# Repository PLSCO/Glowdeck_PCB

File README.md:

# Glowdeck_PCB
Glowdeck circuit board design and layout

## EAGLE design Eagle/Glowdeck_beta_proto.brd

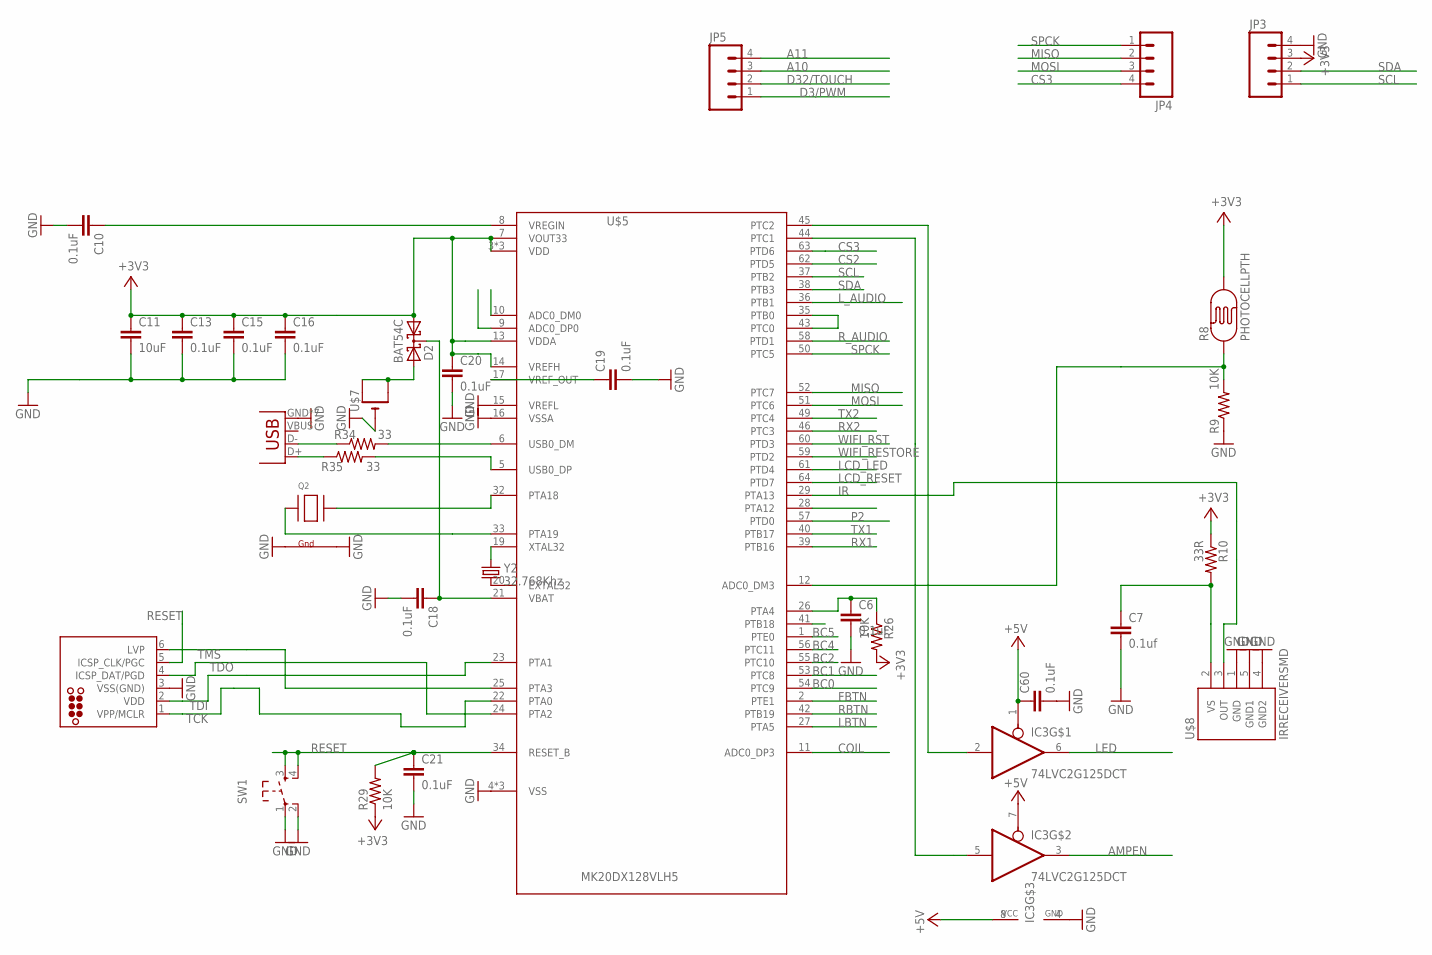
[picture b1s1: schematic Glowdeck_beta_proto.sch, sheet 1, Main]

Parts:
C6, C10, C13, C15, C16, C18, C19, C20, C21, C60: 0.1uF; 0603-CAP
C7: 0.1uf; 0603-CAP
C11: 10uF; 0805
D2: BAT54C; SOT23
IC3: 74LVC2G125DCT; SSOP08
J2: TC2030-MCP-NL
JP3, JP4, JP5: M04LOCK; 1X04_LOCK
Q2: XTAL-4-3225; NX3225
R8: PHOTOCELLPTH; PHOTOCELL
R9, R26, R29: 10K; 0603-RES
R10: 33R; 0603-RES
R34, R35: 33; 0603-RES
SW1: SW_TACT_4P; SW_TACT_SMALL
U$5: MK20DX128VLH5
U$7: CR1220THM; CR1220-THM
U$8: IRRECEIVERSMD; TSOP8523
X3: USB-MICROB
Y2: 32.768Khz; RESONATOR_EPSON_FC_145

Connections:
+3V3: C11.1, C13.1, C15.1, C16.1, C20.1, D2.1 (A1), JP3.3, R8.2, R10.1, R26.2, R29.1, U$5.3 (VDD), U$5.7 (VOUT33), U$5.13 (VDDA), U$5.14 (VREFH), U$5.30 (VDD), U$5.48 (VDD); also elsewhere on the board
+5V: C60.1, IC3.1 (OE), IC3.7 (OE), IC3.8 (VCC); also elsewhere on the board
A10: JP5.3, U$5.9 (ADC0_DP0)
A11: JP5.4, U$5.10 (ADC0_DM0)
AMPEN: IC3.3 (O); also elsewhere on the board
BC0: U$5.54 (PTC9); also elsewhere on the board
BC1: U$5.53 (PTC8); also elsewhere on the board
BC2: U$5.55 (PTC10); also elsewhere on the board
BC4: U$5.56 (PTC11); also elsewhere on the board
BC5: U$5.1 (PTE0); also elsewhere on the board
COIL: U$5.11 (ADC0_DP3); also elsewhere on the board
CS2: U$5.62 (PTD5); also elsewhere on the board
CS3: JP4.4, U$5.63 (PTD6)
D3/PWM: JP5.1, U$5.28 (PTA12)
D32/TOUCH: JP5.2, U$5.41 (PTB18)
FBTN: U$5.2 (PTE1); also elsewhere on the board
GND: C6.2, C7.2, C10.2, C11.2, C13.2, C15.2, C16.2, C18.2, C19.2, C20.2, C21.2, C60.2, IC3.4 (GND), J2.3 (VSS(GND)), JP3.4, Q2.2 (G2), Q2.4 (G1), R9.1, SW1.1, SW1.2, U$5.4 (VSS), U$5.15 (VREFL), U$5.16 (VSSA), U$5.31 (VSS), U$5.47 (VSS), U$7.-, U$8.1 (GND), U$8.4 (GND2), U$8.5 (GND1), X3.GND, X3.P1 (GND), X3.P2 (GND), X3.P3 (GND), X3.P4 (GND), X3.P5 (GND), X3.P6 (GND); also elsewhere on the board
IR: U$5.29 (PTA13), U$8.3 (OUT)
LBTN: U$5.27 (PTA5); also elsewhere on the board
LCD_LED: U$5.61 (PTD4); also elsewhere on the board
LCD_RESET: U$5.64 (PTD7); also elsewhere on the board
LED: IC3.6 (O); also elsewhere on the board
L_AUDIO: U$5.36 (PTB1); also elsewhere on the board
MISO: JP4.2, U$5.52 (PTC7); also elsewhere on the board
MOSI: JP4.3, U$5.51 (PTC6); also elsewhere on the board
unnamed: U$5.35 (PTB0), U$5.43 (PTC0)
unnamed: C7.1, R10.2, U$8.2 (VS)
unnamed: Q2.3 (X2), U$5.32 (PTA18)
unnamed: D2.2 (A2), U$7.+1 (+), U$7.+2 (+1)
unnamed: C6.1, R26.1, U$5.26 (PTA4)
unnamed: U$5.20 (EXTAL32), Y2.P$2 (2)
unnamed: C19.1, U$5.17 (VREF_OUT)
unnamed: C10.1, U$5.8 (VREGIN)
unnamed: C18.1, D2.3 (CC), U$5.21 (VBAT)
unnamed: R34.2, U$5.6 (USB0_DM)
unnamed: R35.2, U$5.5 (USB0_DP)
unnamed: U$5.19 (XTAL32), Y2.P$1 (1)
unnamed: Q2.1 (X1), U$5.33 (PTA19)
unnamed: R8.1, R9.2, U$5.12 (ADC0_DM3)
unnamed: IC3.5 (I), U$5.44 (PTC1)
unnamed: IC3.2 (I), U$5.45 (PTC2)
unnamed: R34.1, X3.D-
unnamed: R35.1, X3.D+
P2: U$5.57 (PTD0); also elsewhere on the board
RBTN: U$5.42 (PTB19); also elsewhere on the board
RESET: C21.1, J2.5 (ICSP_CLK/PGC), R29.2, SW1.3, SW1.4, U$5.34 (RESET_B)
RX1: U$5.39 (PTB16); also elsewhere on the board
RX2: U$5.46 (PTC3); also elsewhere on the board
R_AUDIO: U$5.58 (PTD1); also elsewhere on the board
SCL: JP3.1, U$5.37 (PTB2)
SDA: JP3.2, U$5.38 (PTB3)
SPCK: JP4.1, U$5.50 (PTC5); also elsewhere on the board
TCK: J2.1 (VPP/MCLR), U$5.22 (PTA0)
TDI: J2.2 (VDD), U$5.23 (PTA1)
TDO: J2.4 (ICSP_DAT/PGD), U$5.24 (PTA2)
TMS: J2.6 (LVP), U$5.25 (PTA3)
TX1: U$5.40 (PTB17); also elsewhere on the board
TX2: U$5.49 (PTC4); also elsewhere on the board
WIFI_RESTORE: U$5.59 (PTD2); also elsewhere on the board
WIFI_RST: U$5.60 (PTD3); also elsewhere on the board

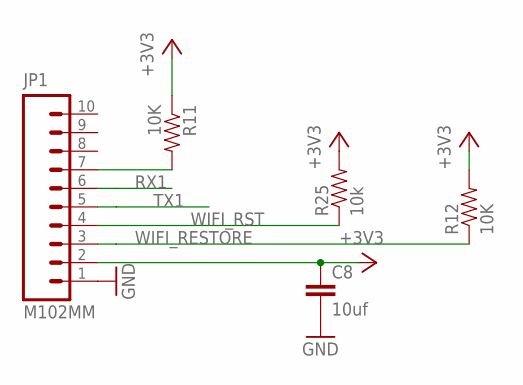
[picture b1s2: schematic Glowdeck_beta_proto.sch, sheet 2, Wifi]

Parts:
C8: 10uf; 0805
JP1: M102MM; 1X10-2MM
R11, R12: 10K; 0603-RES
R25: 10k; 0603-RES

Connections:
+3V3: C8.1, JP1.2, R11.1, R12.2, R25.2; also elsewhere on the board
GND: C8.2, JP1.1; also elsewhere on the board
unnamed: JP1.7, R11.2
RX1: JP1.6; also elsewhere on the board
TX1: JP1.5; also elsewhere on the board
WIFI_RESTORE: JP1.3, R12.1; also elsewhere on the board
WIFI_RST: JP1.4, R25.1; also elsewhere on the board

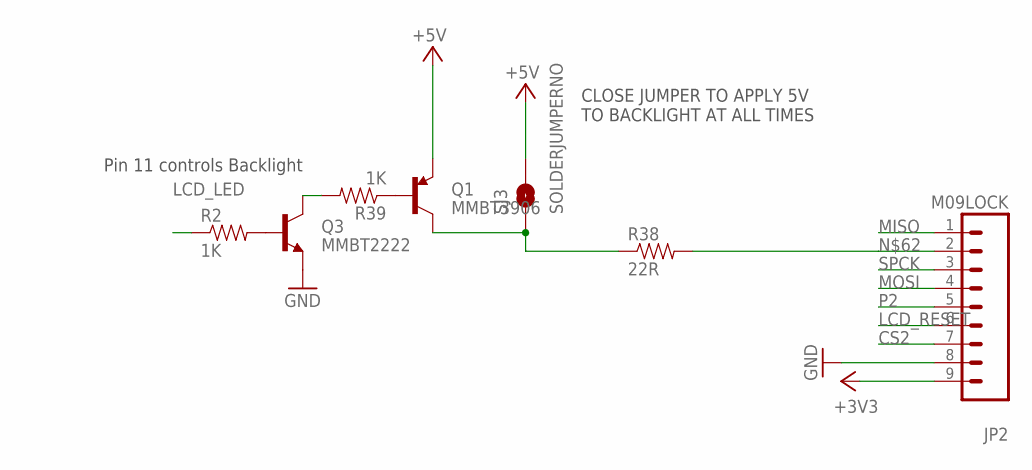
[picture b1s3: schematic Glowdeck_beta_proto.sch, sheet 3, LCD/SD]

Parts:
JP2: M09LOCK; 1X09_LOCK
Q1: MMBT3906; SOT23-3
Q3: MMBT2222; SOT23-3
R2, R39: 1K; 0603-RES
R38: 22R; 1206
SJ3: SOLDERJUMPERNO; SJ_2S-NO

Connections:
+3V3: JP2.9; also elsewhere on the board
+5V: Q1.2 (E), SJ3.2; also elsewhere on the board
BACKLIGHT: Q1.3 (C), R38.1, SJ3.1
CS2: JP2.7; also elsewhere on the board
GND: JP2.8, Q3.2 (E); also elsewhere on the board
LCD_LED: R2.1; also elsewhere on the board
LCD_RESET: JP2.6; also elsewhere on the board
MISO: JP2.1; also elsewhere on the board
MOSI: JP2.4; also elsewhere on the board
unnamed: Q1.1 (B), R39.1
unnamed: JP2.2, R38.2
unnamed: Q3.3 (C), R39.2
unnamed: Q3.1 (B), R2.2
P2: JP2.5; also elsewhere on the board
SPCK: JP2.3; also elsewhere on the board

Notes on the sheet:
CLOSE JUMPER TO APPLY 5V TO BACKLIGHT AT ALL TIMES
Pin 11 controls Backlight

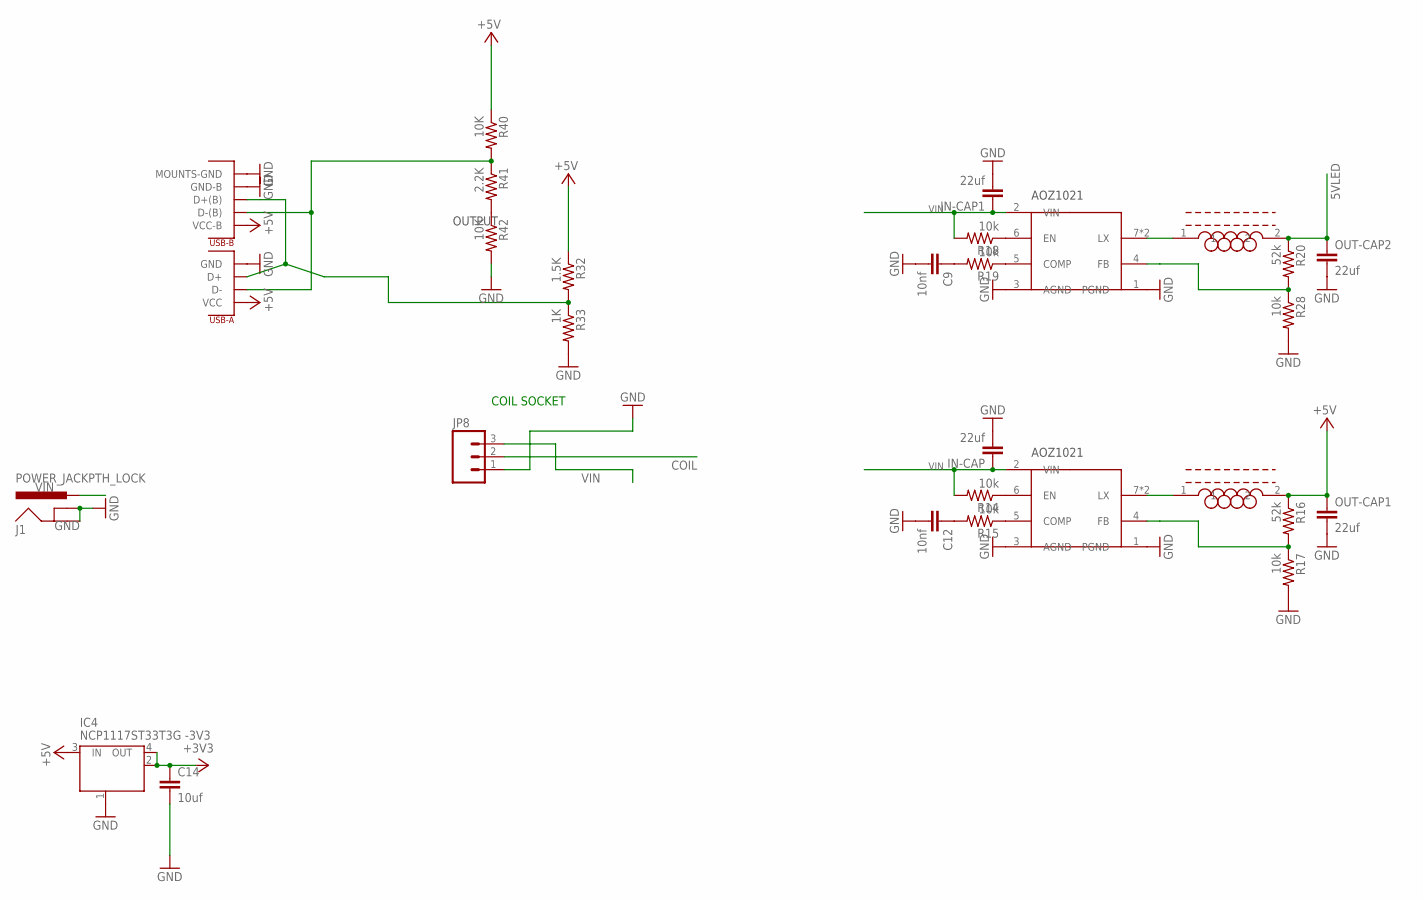
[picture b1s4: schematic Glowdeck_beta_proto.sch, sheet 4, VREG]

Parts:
AOZ1015AI, AOZ1015AI1: AOZ1021; SO-08
C9, C12: 10nf; 0603-CAP
C14: 10uf; 0805
IC4: NCP1117ST33T3G -3V3; SOT223
IN-CAP, IN-CAP1: 22uf; 1210
J1: POWER_JACKPTH_LOCK; POWER_JACK_PTH_LOCK
JP8: M03JST-PTH; JST-3-PTH
OUT-CAP1, OUT-CAP2: 22uf; 1210
R14, R15, R17, R18, R19, R28: 10k; 0603-RES
R16, R20: 52k; 0603-RES
R32: 1.5K; 0603-RES
R33: 1K; 0603-RES
R40, R42: 10K; 0603-RES
R41: 2.2K; 0603-RES
U$1, U$2: SRP7030F; SRP7030
U$6: DUAL-PORT-USB-REC; DUAL-PORT-USB

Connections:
5VLED: OUT-CAP2.1, R20.1, U$2.2; also elsewhere on the board
+3V3: C14.1, IC4.2 (OUT), IC4.4 (OUT); also elsewhere on the board
+5V: IC4.3 (IN), OUT-CAP1.1, R16.1, R32.1, R40.1, U$1.2, U$6.P$10 (VCC-B), U$6.P$12 (VCC); also elsewhere on the board
COIL: JP8.2; also elsewhere on the board
GND: AOZ1015AI.1 (PGND), AOZ1015AI.3 (AGND), AOZ1015AI1.1 (PGND), AOZ1015AI1.3 (AGND), C9.2, C12.2, C14.2, IC4.1 (GND/ADJ), IN-CAP.2, IN-CAP1.2, J1.GND, J1.GNDBREAK, JP8.1, OUT-CAP1.2, OUT-CAP2.2, R17.2, R28.2, R33.2, R42.2, U$6.GND (MOUNTS-GND), U$6.P$2 (MOUNTS-GND), U$6.P$3 (MOUNTS-GND), U$6.P$4 (MOUNTS-GND), U$6.P$9 (GND-B), U$6.P$11 (GND); also elsewhere on the board
LOUT: AOZ1015AI.7 (LX), AOZ1015AI.8 (LX), U$1.1
LOUT1: AOZ1015AI1.7 (LX), AOZ1015AI1.8 (LX), U$2.1
unnamed: AOZ1015AI1.6 (EN), R18.1
unnamed: AOZ1015AI.6 (EN), R14.1
unnamed: AOZ1015AI1.5 (COMP), R19.1
unnamed: C9.1, R19.2
unnamed: AOZ1015AI.5 (COMP), R15.1
unnamed: C12.1, R15.2
unnamed: AOZ1015AI.4 (FB), R16.2, R17.1
unnamed: AOZ1015AI1.4 (FB), R20.2, R28.1
unnamed: R32.2, R33.1, U$6.P$6 (D+(B)), U$6.P$8 (D+)
unnamed: R41.2, R42.1
unnamed: R40.2, R41.1, U$6.P$5 (D-(B)), U$6.P$7 (D-)
VIN: AOZ1015AI.2 (VIN), AOZ1015AI1.2 (VIN), IN-CAP.1, IN-CAP1.1, J1.PWR, JP8.3, R14.2, R18.2; also elsewhere on the board

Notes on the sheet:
OUTPUT
COIL SOCKET

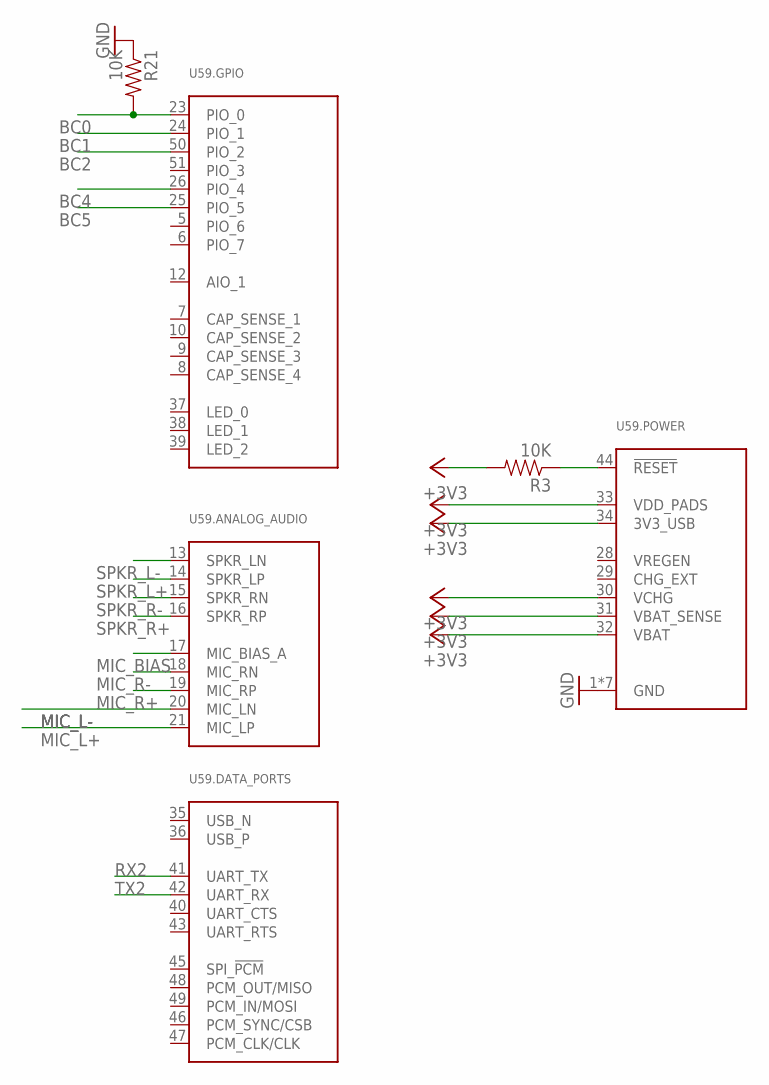
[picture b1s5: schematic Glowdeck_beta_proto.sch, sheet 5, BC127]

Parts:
R3, R21: 10K; 0603-RES
U59: BC127EXTRA_PASTE; BC127_XTRA_PASTE

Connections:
+3V3: R3.2, U59.30 (VCHG), U59.31 (VBAT_SENSE), U59.32 (VBAT), U59.33 (VDD_PADS), U59.34 (3V3_USB); also elsewhere on the board
BC0: R21.2, U59.23 (PIO_0); also elsewhere on the board
BC1: U59.24 (PIO_1); also elsewhere on the board
BC2: U59.50 (PIO_2); also elsewhere on the board
BC4: U59.26 (PIO_4); also elsewhere on the board
BC5: U59.25 (PIO_5); also elsewhere on the board
GND: R21.1, U59.1 (GND), U59.2 (GND), U59.3 (GND), U59.4 (GND), U59.11 (GND), U59.22 (GND), U59.27 (GND); also elsewhere on the board
MIC_BIAS: U59.17 (MIC_BIAS_A); also elsewhere on the board
MIC_L+: U59.21 (MIC_LP); also elsewhere on the board
MIC_L-: U59.20 (MIC_LN); also elsewhere on the board
MIC_R+: U59.19 (MIC_RP)
MIC_R-: U59.18 (MIC_RN)
unnamed: R3.1, U59.44 (!RESET)
RX2: U59.41 (UART_TX); also elsewhere on the board
SPKR_L+: U59.14 (SPKR_LP); also elsewhere on the board
SPKR_L-: U59.13 (SPKR_LN); also elsewhere on the board
SPKR_R+: U59.16 (SPKR_RP); also elsewhere on the board
SPKR_R-: U59.15 (SPKR_RN); also elsewhere on the board
TX2: U59.42 (UART_RX); also elsewhere on the board

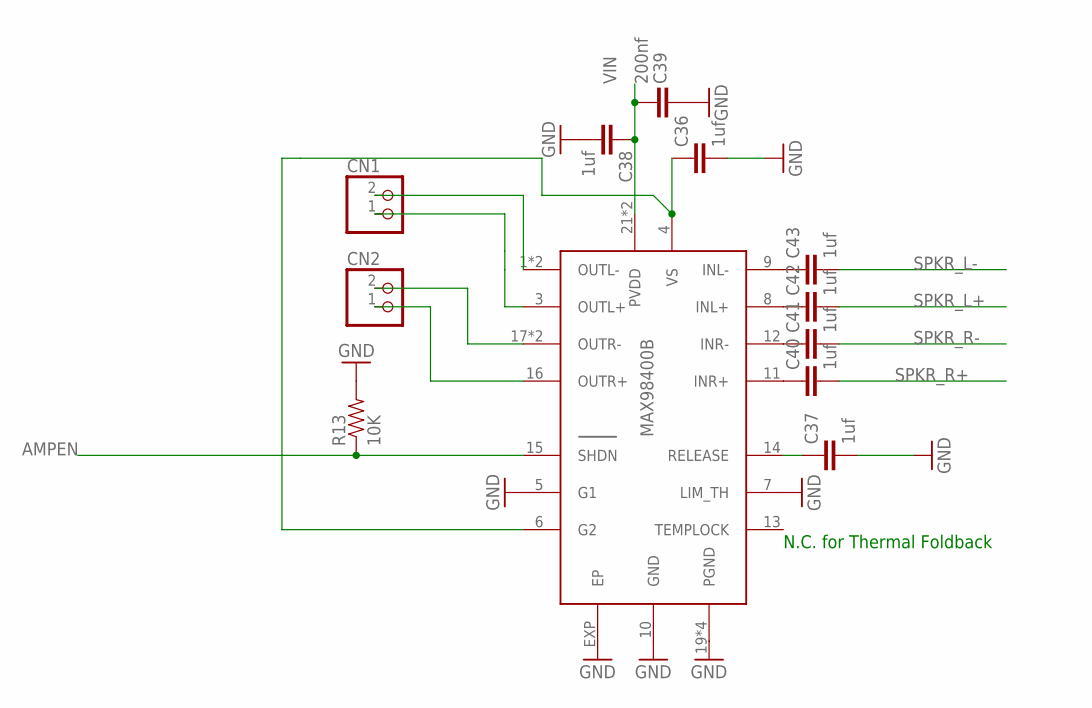
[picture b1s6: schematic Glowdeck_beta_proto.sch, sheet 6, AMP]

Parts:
C36, C37, C38, C40, C41, C42, C43: 1uf; 0805
C39: 200nf; 0603-CAP
CN1, CN2: JST_2PIN-THM; JST-PH-2-THM
R13: 10K; 0603-RES
U$3: MAX98400B; TQFN24-EP

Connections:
AMPEN: R13.1, U$3.15 (SHDN); also elsewhere on the board
GND: C36.2, C37.2, C38.2, C39.1, R13.2, U$3.5 (G1), U$3.7 (LIM_TH), U$3.10 (GND), U$3.19 (PGND), U$3.20 (PGND), U$3.23 (PGND), U$3.24 (PGND), U$3.EXP (EP); also elsewhere on the board
unnamed: C40.1, U$3.11 (INR+)
unnamed: C41.1, U$3.12 (INR-)
unnamed: C42.1, U$3.8 (INL+)
unnamed: C43.1, U$3.9 (INL-)
unnamed: CN2.1 (2), U$3.16 (OUTR+)
unnamed: CN2.2 (1), U$3.17 (OUTR-), U$3.18 (OUTR-)
unnamed: CN1.1 (2), U$3.3 (OUTL+)
unnamed: CN1.2 (1), U$3.1 (OUTL-), U$3.2 (OUTL-)
unnamed: C37.1, U$3.14 (RELEASE)
unnamed: C36.1, U$3.4 (VS), U$3.6 (G2)
SPKR_L+: C42.2; also elsewhere on the board
SPKR_L-: C43.2; also elsewhere on the board
SPKR_R+: C40.2; also elsewhere on the board
SPKR_R-: C41.2; also elsewhere on the board
VIN: C38.1, C39.2, U$3.21 (PVDD), U$3.22 (PVDD); also elsewhere on the board

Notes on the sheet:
N.C. for Thermal Foldback

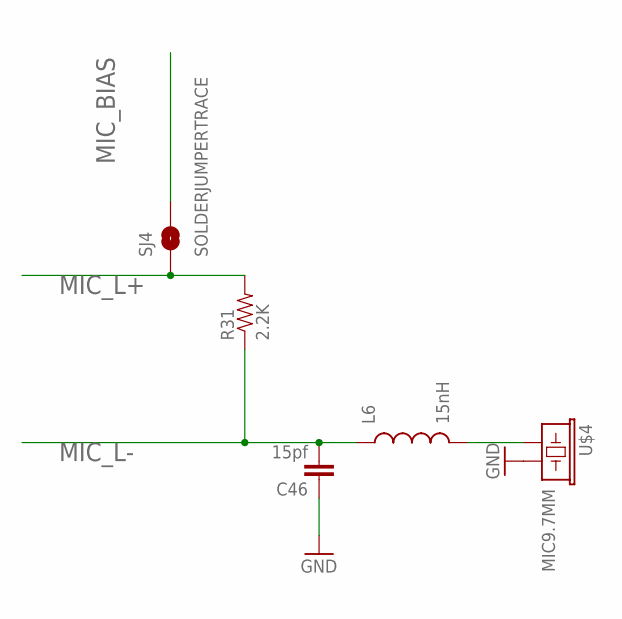
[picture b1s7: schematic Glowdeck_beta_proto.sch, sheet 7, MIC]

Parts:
C46: 15pf; 0805
L6: 15nH; 0603
R31: 2.2K; 0603-RES
SJ4: SOLDERJUMPERTRACE; SJ_2S-TRACE
U$4: MIC9.7MM; MIC-9.7MM

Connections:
GND: C46.1, U$4.2; also elsewhere on the board
MIC_BIAS: SJ4.2; also elsewhere on the board
MIC_L+: R31.2, SJ4.1; also elsewhere on the board
MIC_L-: C46.2, L6.1, R31.1; also elsewhere on the board
unnamed: L6.2, U$4.1

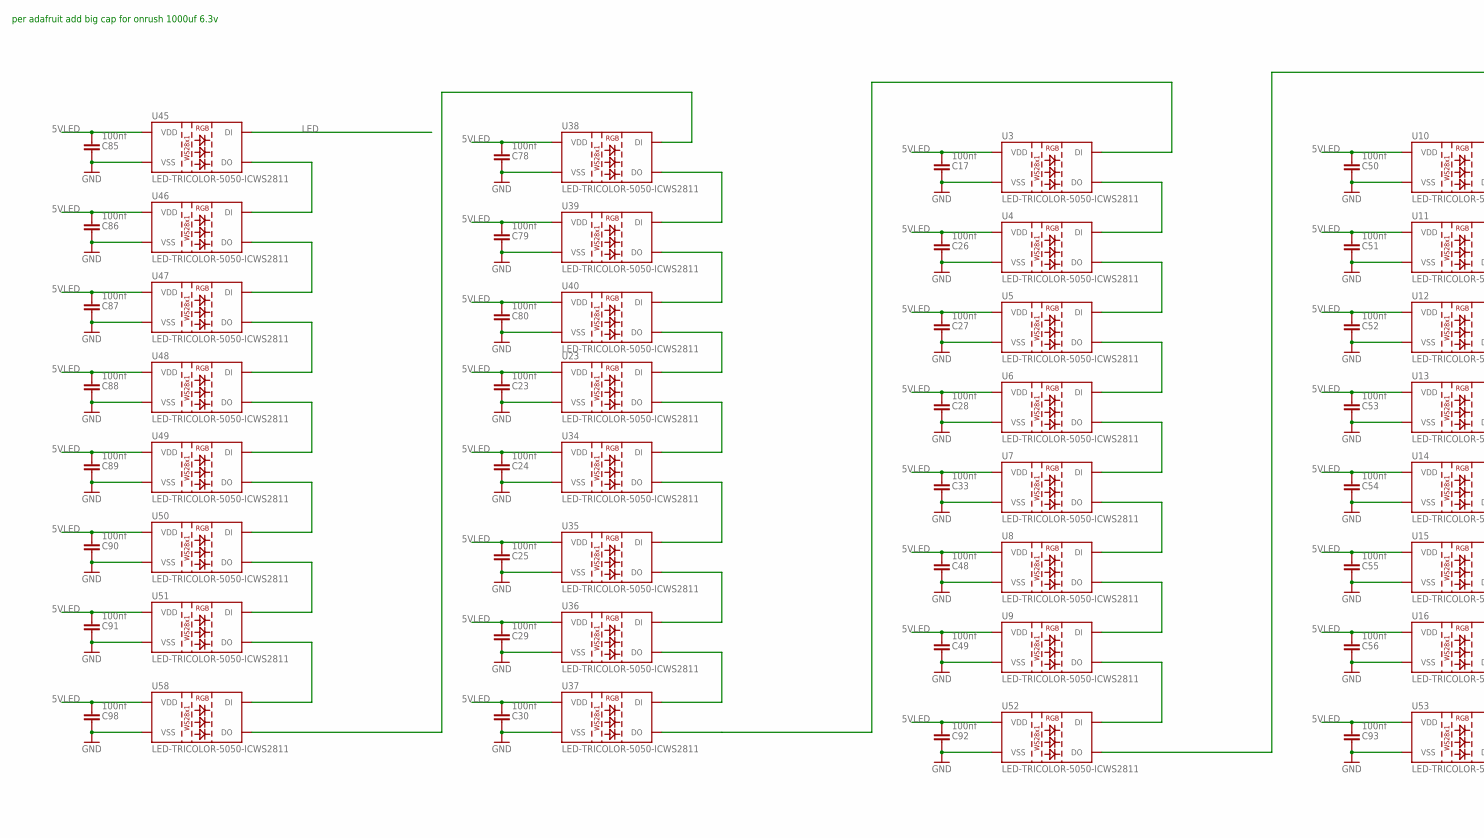
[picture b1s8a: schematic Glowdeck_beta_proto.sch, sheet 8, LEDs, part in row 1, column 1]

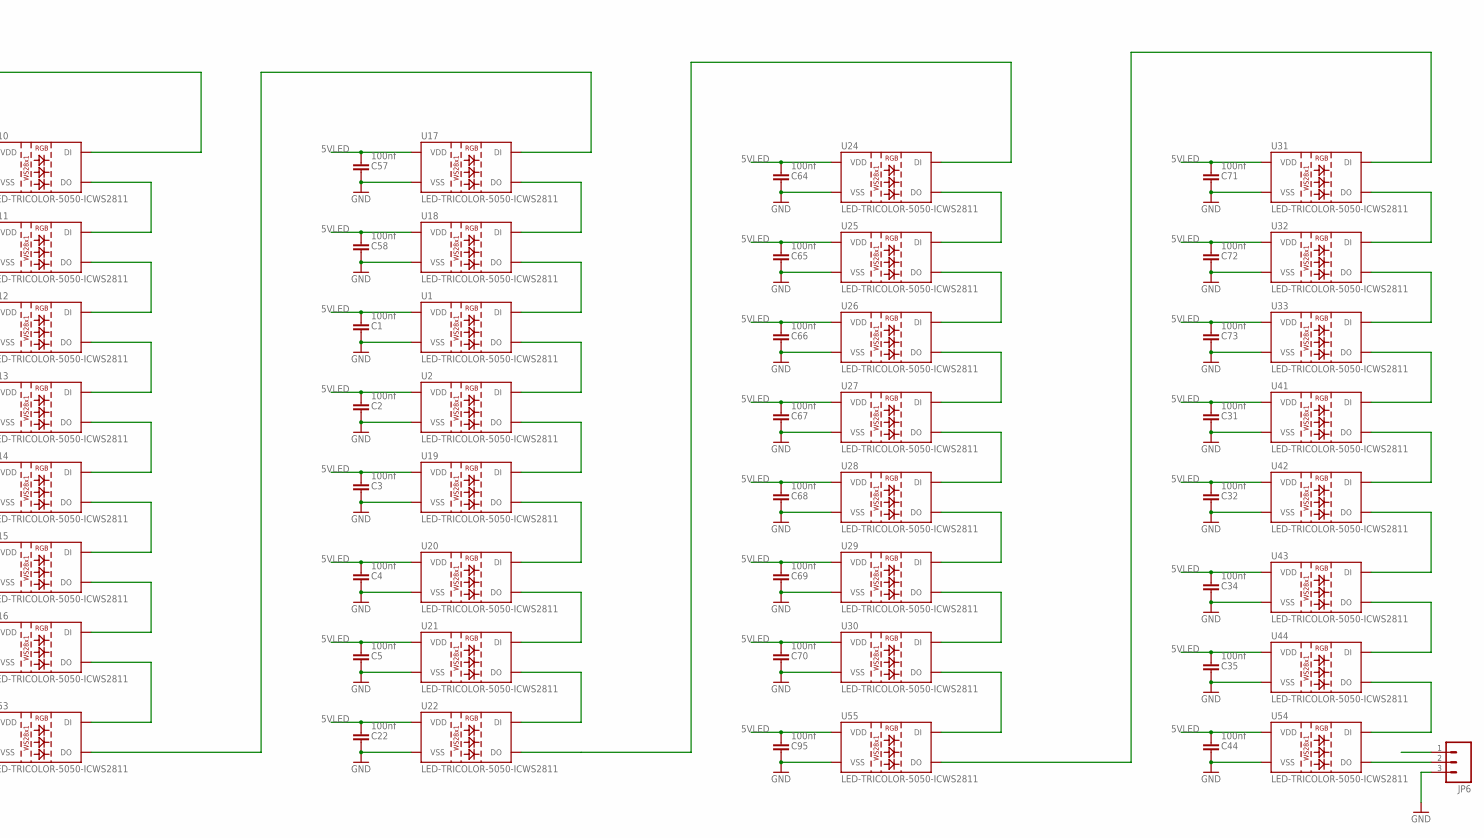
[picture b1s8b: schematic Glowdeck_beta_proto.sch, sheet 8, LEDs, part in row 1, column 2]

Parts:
C1, C2, C3, C4, C5, C17, C22, C23, C24, C25, C26, C27, C28, C29, C30, C31, C32, C33, C34, C35, C44, C48, C49, C50, C51, C52, C53, C54, C55, C56, C57, C58, C64, C65, C66, C67, C68, C69, C70, C71, C72, C73, C78, C79, C80, C85, C86, C87, C88, C89, C90, C91, C92, C93, C95, C98: 100nf; 0603-CAP
JP6: M03LOCK; 1X03_LOCK
U1, U2, U3, U4, U5, U6, U7, U8, U9, U10, U11, U12, U13, U14, U15, U16, U17, U18, U19, U20, U21, U22, U23, U24, U25, U26, U27, U28, U29, U30, U31, U32, U33, U34, U35, U36, U37, U38, U39, U40, U41, U42, U43, U44, U45, U46, U47, U48, U49, U50, U51, U52, U53, U54, U55, U58: LED-TRICOLOR-5050-ICWS2811; LED-TRICOLOR-5050-IC

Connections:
5VLED: C1.2, C2.2, C3.2, C4.2, C5.2, C17.2, C22.2, C23.2, C24.2, C25.2, C26.2, C27.2, C28.2, C29.2, C30.2, C31.2, C32.2, C33.2, C34.2, C35.2, C44.2, C48.2, C49.2, C50.2, C51.2, C52.2, C53.2, C54.2, C55.2, C56.2, C57.2, C58.2, C64.2, C65.2, C66.2, C67.2, C68.2, C69.2, C70.2, C71.2, C72.2, C73.2, C78.2, C79.2, C80.2, C85.2, C86.2, C87.2, C88.2, C89.2, C90.2, C91.2, C92.2, C93.2, C95.2, C98.2, JP6.1, U1.1 (VDD), U2.1 (VDD), U3.1 (VDD), U4.1 (VDD), U5.1 (VDD), U6.1 (VDD), U7.1 (VDD), U8.1 (VDD), U9.1 (VDD), U10.1 (VDD), U11.1 (VDD), U12.1 (VDD), U13.1 (VDD), U14.1 (VDD), U15.1 (VDD), U16.1 (VDD), U17.1 (VDD), U18.1 (VDD), U19.1 (VDD), U20.1 (VDD), U21.1 (VDD), U22.1 (VDD), U23.1 (VDD), U24.1 (VDD), U25.1 (VDD), U26.1 (VDD), U27.1 (VDD), U28.1 (VDD), U29.1 (VDD), U30.1 (VDD), U31.1 (VDD), U32.1 (VDD), U33.1 (VDD), U34.1 (VDD), U35.1 (VDD), U36.1 (VDD), U37.1 (VDD), U38.1 (VDD), U39.1 (VDD), U40.1 (VDD), U41.1 (VDD), U42.1 (VDD), U43.1 (VDD), U44.1 (VDD), U45.1 (VDD), U46.1 (VDD), U47.1 (VDD), U48.1 (VDD), U49.1 (VDD), U50.1 (VDD), U51.1 (VDD), U52.1 (VDD), U53.1 (VDD), U54.1 (VDD), U55.1 (VDD), U58.1 (VDD); also elsewhere on the board
GND: C1.1, C2.1, C3.1, C4.1, C5.1, C17.1, C22.1, C23.1, C24.1, C25.1, C26.1, C27.1, C28.1, C29.1, C30.1, C31.1, C32.1, C33.1, C34.1, C35.1, C44.1, C48.1, C49.1, C50.1, C51.1, C52.1, C53.1, C54.1, C55.1, C56.1, C57.1, C58.1, C64.1, C65.1, C66.1, C67.1, C68.1, C69.1, C70.1, C71.1, C72.1, C73.1, C78.1, C79.1, C80.1, C85.1, C86.1, C87.1, C88.1, C89.1, C90.1, C91.1, C92.1, C93.1, C95.1, C98.1, JP6.3, U1.3 (VSS), U2.3 (VSS), U3.3 (VSS), U4.3 (VSS), U5.3 (VSS), U6.3 (VSS), U7.3 (VSS), U8.3 (VSS), U9.3 (VSS), U10.3 (VSS), U11.3 (VSS), U12.3 (VSS), U13.3 (VSS), U14.3 (VSS), U15.3 (VSS), U16.3 (VSS), U17.3 (VSS), U18.3 (VSS), U19.3 (VSS), U20.3 (VSS), U21.3 (VSS), U22.3 (VSS), U23.3 (VSS), U24.3 (VSS), U25.3 (VSS), U26.3 (VSS), U27.3 (VSS), U28.3 (VSS), U29.3 (VSS), U30.3 (VSS), U31.3 (VSS), U32.3 (VSS), U33.3 (VSS), U34.3 (VSS), U35.3 (VSS), U36.3 (VSS), U37.3 (VSS), U38.3 (VSS), U39.3 (VSS), U40.3 (VSS), U41.3 (VSS), U42.3 (VSS), U43.3 (VSS), U44.3 (VSS), U45.3 (VSS), U46.3 (VSS), U47.3 (VSS), U48.3 (VSS), U49.3 (VSS), U50.3 (VSS), U51.3 (VSS), U52.3 (VSS), U53.3 (VSS), U54.3 (VSS), U55.3 (VSS), U58.3 (VSS); also elsewhere on the board
LED: U45.4 (DI); also elsewhere on the board
unnamed: U23.4 (DI), U40.2 (DO)
unnamed: U42.2 (DO), U43.4 (DI)
unnamed: U1.2 (DO), U2.4 (DI)
unnamed: U1.4 (DI), U18.2 (DO)
unnamed: U33.2 (DO), U41.4 (DI)
unnamed: U3.2 (DO), U4.4 (DI)
unnamed: U4.2 (DO), U5.4 (DI)
unnamed: U5.2 (DO), U6.4 (DI)
unnamed: U6.2 (DO), U7.4 (DI)
unnamed: U7.2 (DO), U8.4 (DI)
unnamed: U8.2 (DO), U9.4 (DI)
unnamed: U10.2 (DO), U11.4 (DI)
unnamed: U11.2 (DO), U12.4 (DI)
unnamed: U12.2 (DO), U13.4 (DI)
unnamed: U13.2 (DO), U14.4 (DI)
unnamed: U14.2 (DO), U15.4 (DI)
unnamed: U15.2 (DO), U16.4 (DI)
unnamed: U17.2 (DO), U18.4 (DI)
unnamed: U2.2 (DO), U19.4 (DI)
unnamed: U24.2 (DO), U25.4 (DI)
unnamed: U25.2 (DO), U26.4 (DI)
unnamed: U26.2 (DO), U27.4 (DI)
unnamed: U27.2 (DO), U28.4 (DI)
unnamed: U28.2 (DO), U29.4 (DI)
unnamed: U29.2 (DO), U30.4 (DI)
unnamed: U31.2 (DO), U32.4 (DI)
unnamed: U32.2 (DO), U33.4 (DI)
unnamed: U38.2 (DO), U39.4 (DI)
unnamed: U39.2 (DO), U40.4 (DI)
unnamed: U45.2 (DO), U46.4 (DI)
unnamed: U46.2 (DO), U47.4 (DI)
unnamed: U47.2 (DO), U48.4 (DI)
unnamed: U48.2 (DO), U49.4 (DI)
unnamed: U49.2 (DO), U50.4 (DI)
unnamed: U50.2 (DO), U51.4 (DI)
unnamed: U38.4 (DI), U58.2 (DO)
unnamed: U10.4 (DI), U52.2 (DO)
unnamed: U17.4 (DI), U53.2 (DO)
unnamed: U31.4 (DI), U55.2 (DO)
unnamed: U9.2 (DO), U52.4 (DI)
unnamed: U16.2 (DO), U53.4 (DI)
unnamed: U30.2 (DO), U55.4 (DI)
unnamed: U19.2 (DO), U20.4 (DI)
unnamed: U51.2 (DO), U58.4 (DI)
unnamed: U20.2 (DO), U21.4 (DI)
unnamed: U21.2 (DO), U22.4 (DI)
unnamed: U22.2 (DO), U24.4 (DI)
unnamed: U23.2 (DO), U34.4 (DI)
unnamed: U34.2 (DO), U35.4 (DI)
unnamed: U35.2 (DO), U36.4 (DI)
unnamed: U36.2 (DO), U37.4 (DI)
unnamed: U3.4 (DI), U37.2 (DO)
unnamed: U41.2 (DO), U42.4 (DI)
unnamed: U43.2 (DO), U44.4 (DI)
unnamed: U44.2 (DO), U54.4 (DI)
unnamed: JP6.2, U54.2 (DO)

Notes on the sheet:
per adafruit add big cap for onrush 1000uf 6.3v

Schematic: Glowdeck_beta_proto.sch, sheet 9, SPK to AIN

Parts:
C45, C47: 1uf; 0805
C59: 0.1uf; 0603-CAP
IC2: OPAMP-DUALU; SO08
R1, R6, R23, R24, R27, R30, R36, R37: 10K; 0603-RES
R4, R5, R7, R22: 16K; 0603-RES

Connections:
+3V3: C59.1, IC2.8 (V+), R24.2, R30.2; also elsewhere on the board
GND: C59.2, IC2.4 (V-), R4.2, R22.1, R27.1, R37.1; also elsewhere on the board
L_AUDIO: C45.2, R24.1, R27.2; also elsewhere on the board
L_AUDIO_PRE: C45.1, IC2.1 (OUT), R7.1
unnamed: IC2.5 (+IN), R1.2, R4.1
unnamed: IC2.6 (-IN), R5.1, R36.2
unnamed: IC2.3 (+IN), R22.2, R23.1
unnamed: IC2.2 (-IN), R6.2, R7.2
R_AUDIO: C47.2, R30.1, R37.2; also elsewhere on the board
R_AUDIO_PRE: C47.1, IC2.7 (OUT), R5.2
SPKR_L+: R23.2; also elsewhere on the board
SPKR_L-: R6.1; also elsewhere on the board
SPKR_R+: R1.1; also elsewhere on the board
SPKR_R-: R36.1; also elsewhere on the board

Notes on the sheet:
CIRCUIT ASSUMES DIFFERENTIAL INPUT WILL NOT EXCEED +/- 2V PtoP

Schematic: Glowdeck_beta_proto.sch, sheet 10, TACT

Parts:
S1, S3, S4: SWITCH-MOMENTARY-212MM; TACTILE-PTH-12MM

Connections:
FBTN: S3.3 (2); also elsewhere on the board
GND: S1.1, S3.1, S4.1; also elsewhere on the board
LBTN: S4.3 (2); also elsewhere on the board
RBTN: S1.3 (2); also elsewhere on the board

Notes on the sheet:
RIGHT BUTTON
FRONT BUTTON

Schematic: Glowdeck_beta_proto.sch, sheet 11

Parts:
STANDOFF1, STANDOFF2, STANDOFF3, STANDOFF4, STANDOFF5, STANDOFF6, STANDOFF7, STANDOFF8, STANDOFF9, STANDOFF10, STANDOFF11, STANDOFF12, STANDOFF13, STANDOFF14, STANDOFF15: STAND-OFF

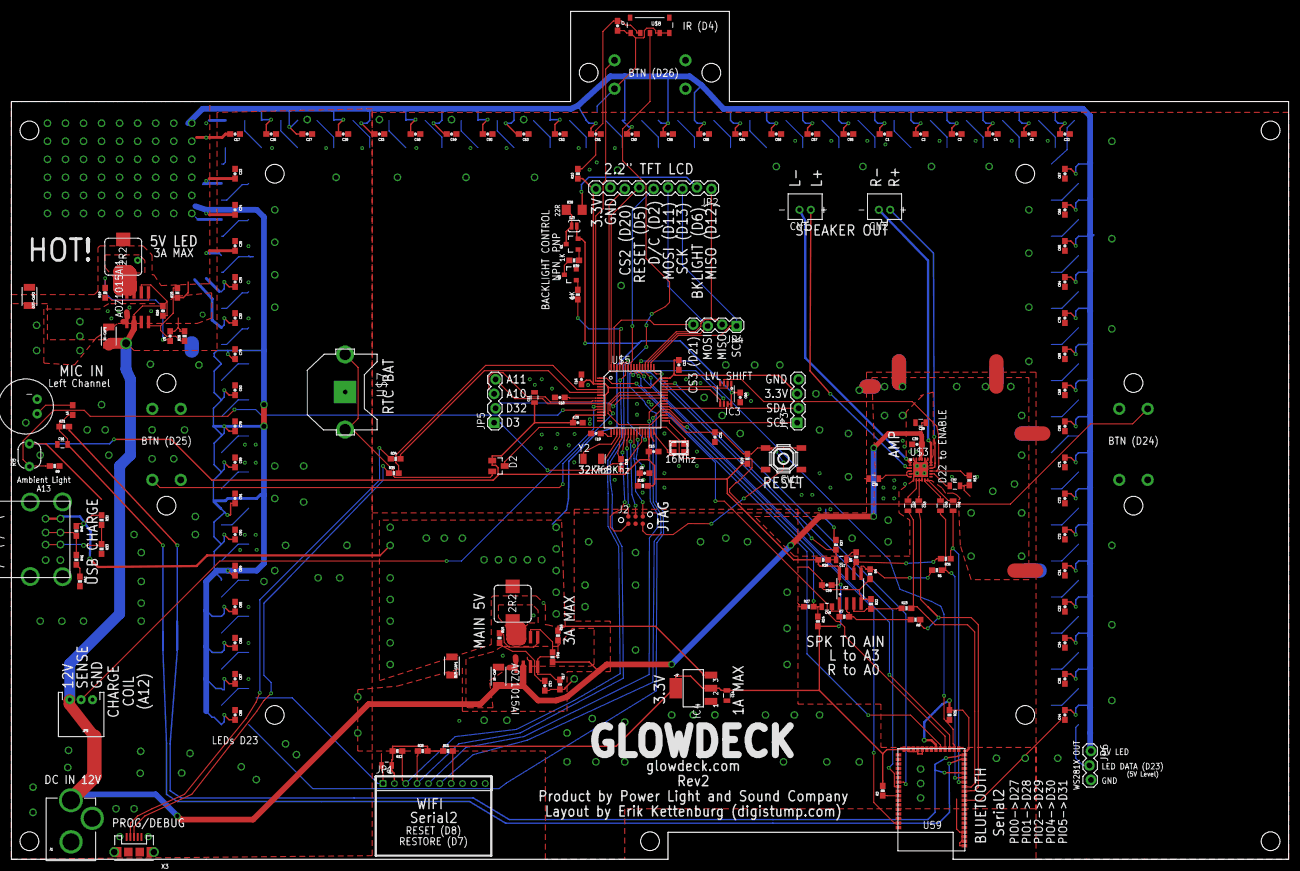
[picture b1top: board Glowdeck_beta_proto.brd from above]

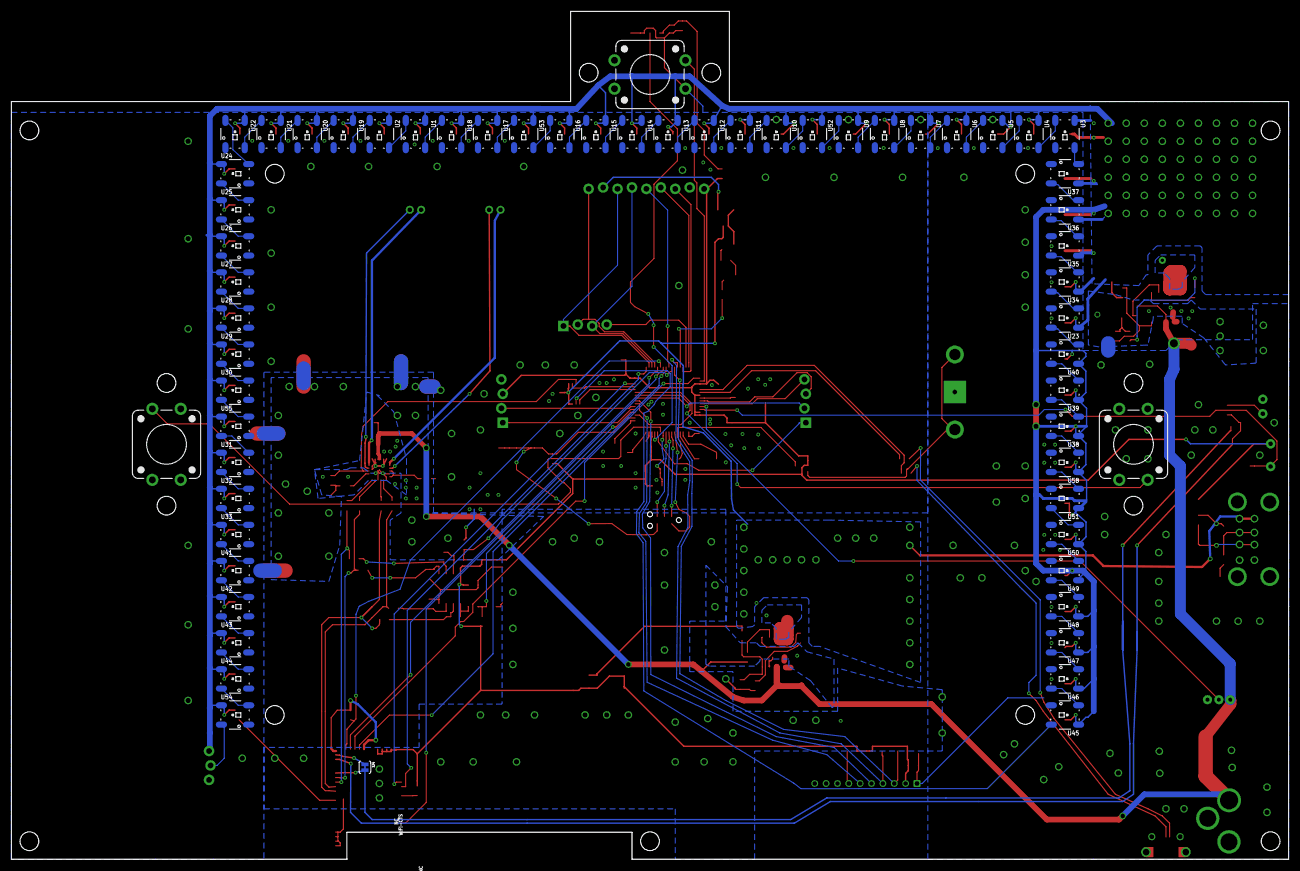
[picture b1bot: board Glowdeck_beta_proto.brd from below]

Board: 2 copper layers, 224.8 x 149.2 mm, 239 parts (60 on the bottom side), 162 nets.

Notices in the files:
parts and their libraries:
SparkFun: Licensing: CC v3.0 Share-Alike You are welcome to use this library for commercial purposes.
tag-connect: ©2009 ROFA.cz - modified and updated by Robert Darlington ‹rdarlington@gmail.com›
